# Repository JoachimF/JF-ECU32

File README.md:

# JF-ECU32
RC Jet Engine ECU

Details ici : https://www.usinages.com/threads/creation-dun-ecu-opensource-pour-micro-reacteur.160245/

## Environement
- VsCode
- IDF 5.0.8

## Démarrage du projet d'ECU opensource pour réacteurs

### Fonctionnalitées :

- Démarrage GAZ/KERO
- Fonctionnement du réacteur*
- Apprentissage du moteur*
- Surveillance des paramètres
- Redémarrage en vol*
- Log
- Interface WEB
- Ecran sans fil*
- Log sur MicroSd
- Baromètre

### Composants :
- Processeur ESP32
- Interface sonde K MAX31855
- INA218
- Max31855K
- BMP280
- MicroSD

### Entrées :
- Entrée 2S - 3S pour accus LIPO ou LIION
- Entrée PPM - Gaz ou SBUS
- Entrée PPM - AUX
- Entrée compte tours IR ou HALL
- Entrée sonde K (module MAX31865)
- INA219 courant de la bougie
- BMP280 pression / altitude

### Sorties :
- Sortie PWM/PPM 10A pour le moteur de démarrage
- Sortie PWM/PPM 10A pour la pompe ou ESC brushless
- Sortie PWM/PPM 10A pour ESC de pompe numéro 2 (fumigène ou redondance, comme sur les grandeurs)
- Sorties PWM pour 2 électrovannes (KERO/GAZ - KERO/KERO) 1A
- Sortie PWM pour une bougies Glow ou Kero 10A
- Sortie FPORT FRSky/Hott/Futaba (télémétrie)*

### Parties fonctionnelles :
 
 #### Entrées
 - Lecture des RPM
 - Lecture EGT
 - Lecture courant bougie
 - Lecture tension de batterie
 - Lecture Voie des gaz et voie aux
 
 #### Sortie   
 - Pilotage starter (PPM ou PWM)
 - Pilotage bougie
 - pilotage pompe1 (PPM ou PWM)
 - pilotage pompe2 (PPM ou PWM)
 - pilotage des vannes

#### Logiciel
 - Ecriture des logs (sur Spiffs pour le moment)
 - Calcul des deltas (EGT - RPM)
 - Calibration du démareur (Récupere les mini maxi en commande (%) et en RPM)
 - Préchauffage au gaz
 - Protection batterie trop faible ou trop haute en tension
 - Refroidissement de la turbine (action du démarreur)

### Parties à coder :
  - Lecture BMP280
  - Log sur MicroSD
  - fonction de démarrage du moteur
  - fonction de pilotage du moteur
  - fonction apprentissage du moteur
  - plein d'autres choses

*en cours de codage

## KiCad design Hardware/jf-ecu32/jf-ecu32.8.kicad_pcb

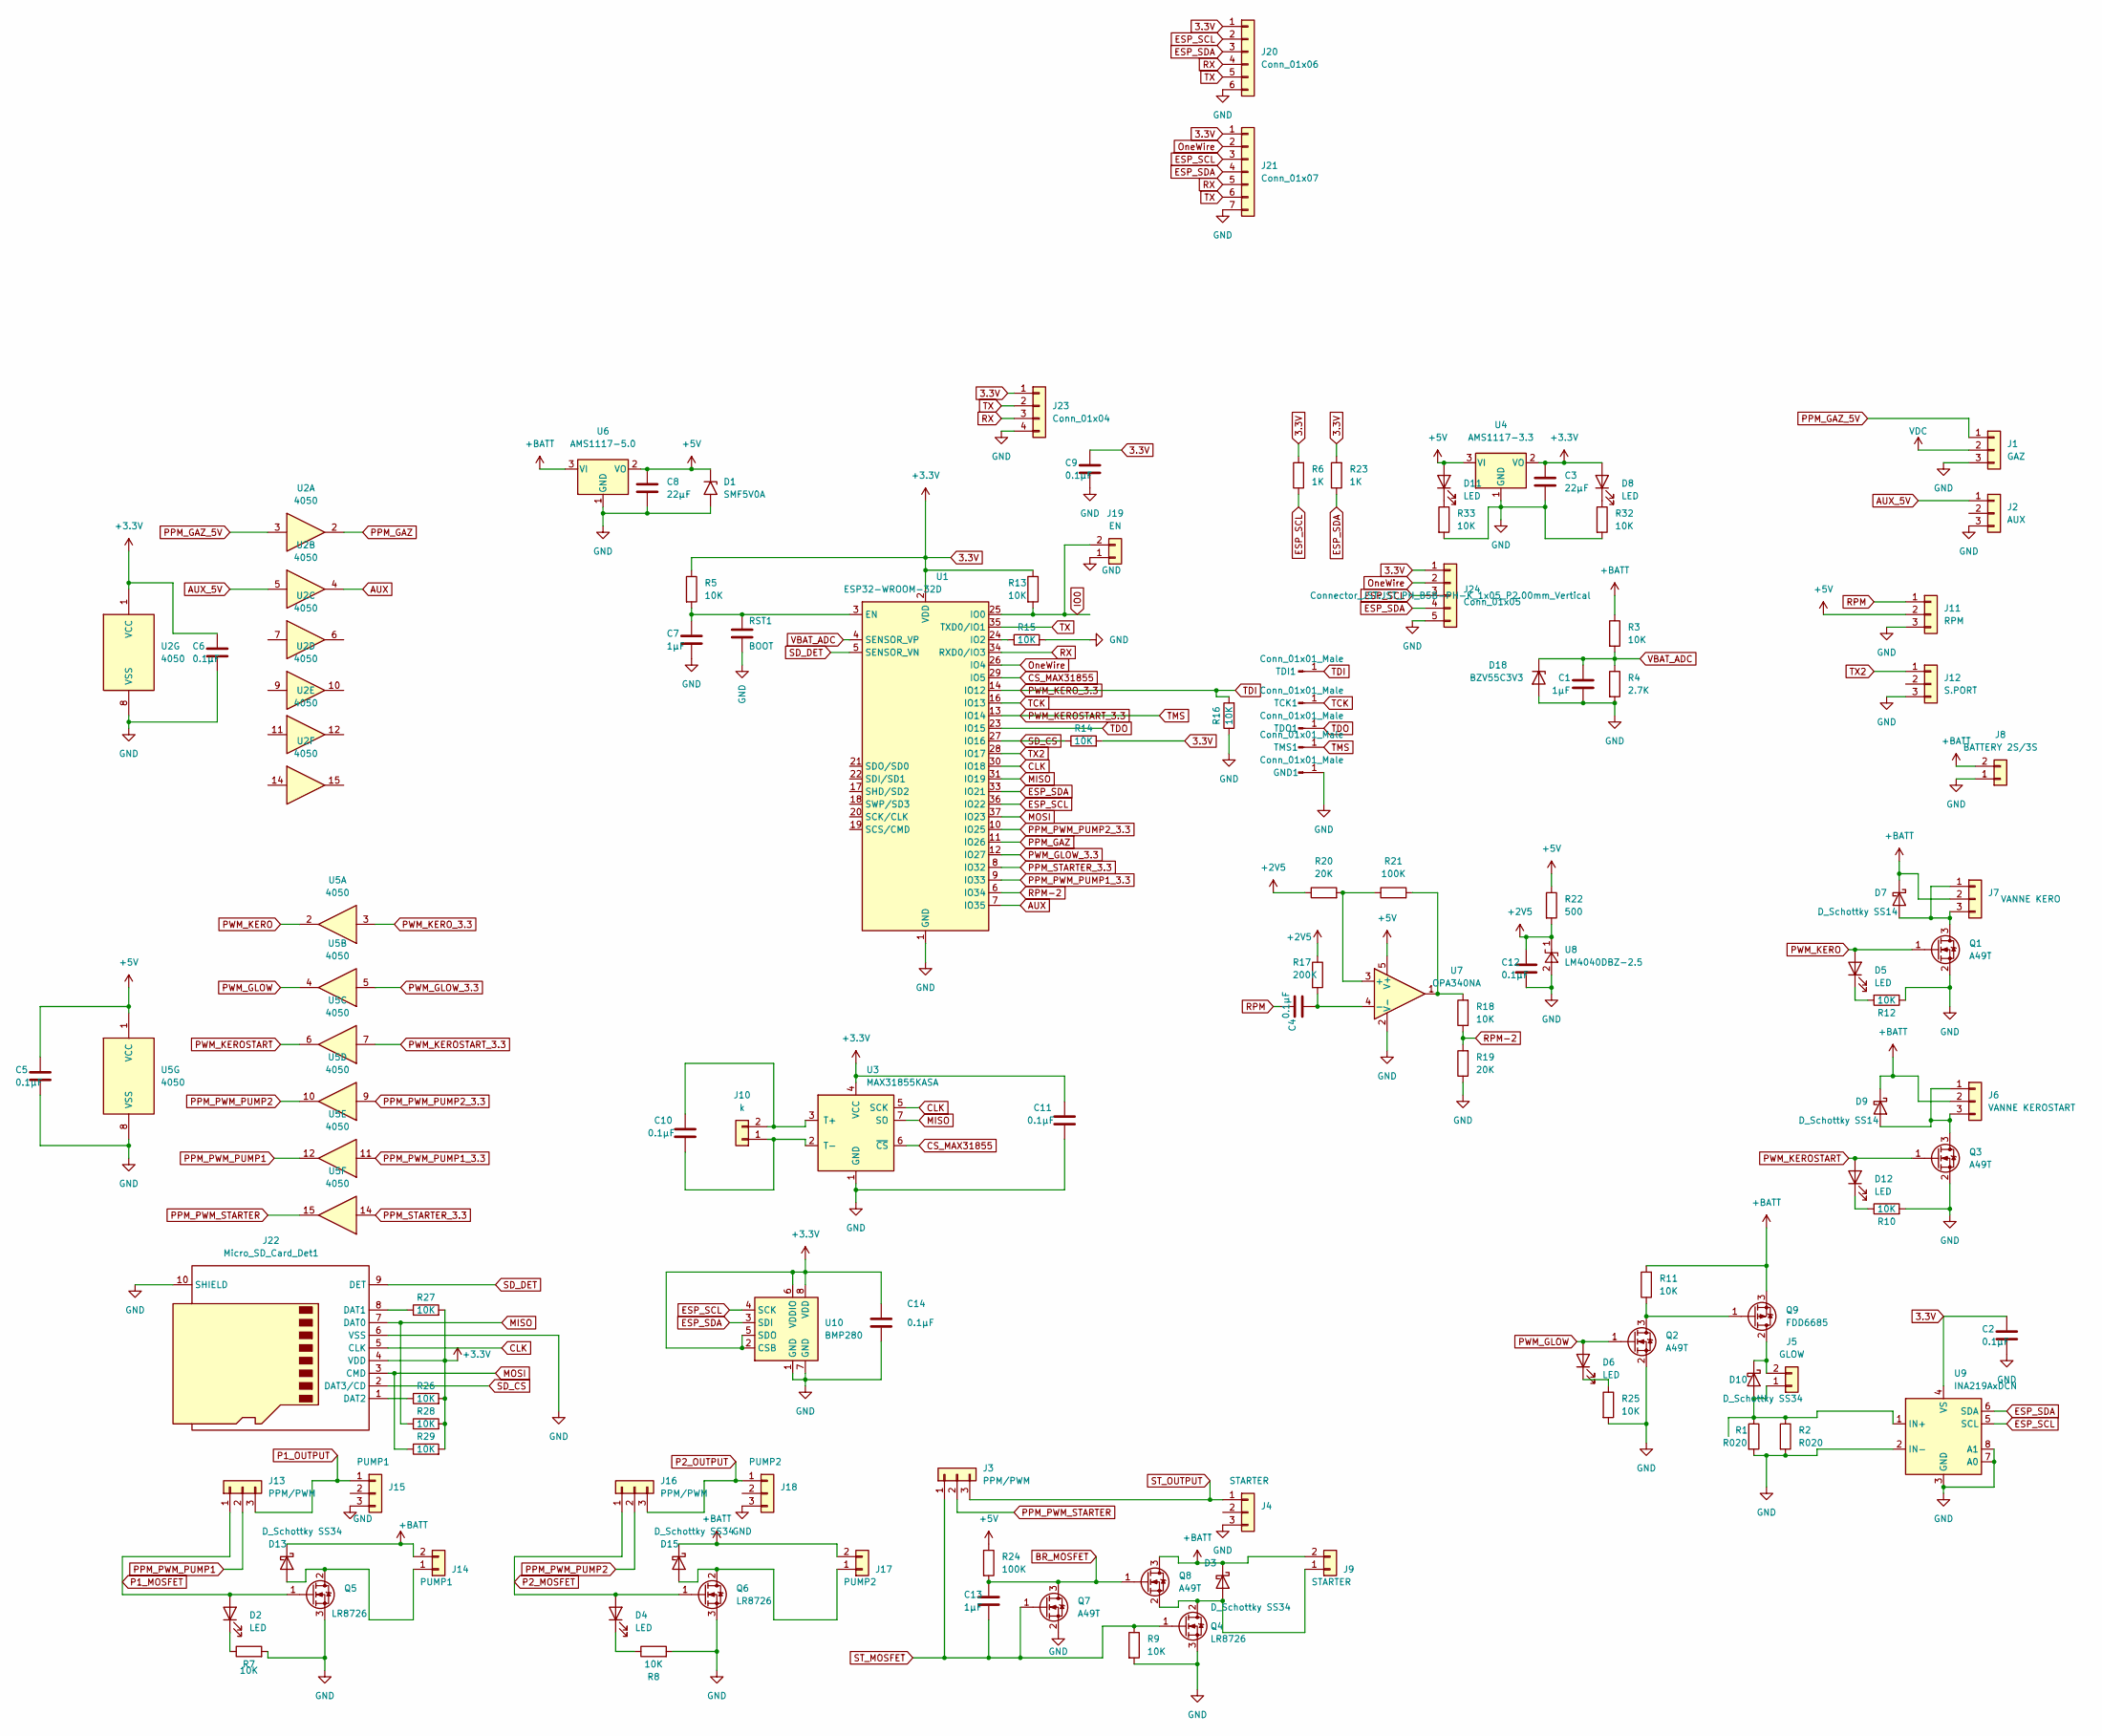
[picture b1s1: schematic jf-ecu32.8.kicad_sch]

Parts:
C1, C7, C13: 1µF; C_0603_1608Metric
C2, C4, C5, C6, C9, C10, C11, C12, C14: 0.1µF; C_0603_1608Metric
C3, C8: 22µF; CP_Elec_5x3
D1: SMF5V0A; D_SMF
D2, D4, D5, D6, D8, D11, D12: LED; LED_0603_1608Metric
D3, D10, D13, D15: D_Schottky SS34; D_SMA
D7, D9: D_Schottky SS14; D_SMA
D18: BZV55C3V3; D_MiniMELF
GND1: Conn_01x01_Male; PinHeader_1x01_P2.00mm_Vertical
J1: GAZ; PinHeader_1x03_P2.54mm_Vertical
J2: AUX; PinHeader_1x03_P2.54mm_Vertical
J3, J13, J16: PPM/PWM; PinHeader_1x03_P2.54mm_Vertical
J4: STARTER; PinHeader_1x03_P2.54mm_Vertical
J5: GLOW; AMASS_XT30U-F_1x02_P5.0mm_Vertical
J6: VANNE KEROSTART; PinHeader_1x03_P2.54mm_Vertical
J7: VANNE KERO; PinHeader_1x03_P2.54mm_Vertical
J8: BATTERY 2S/3S; AMASS_XT30U-M_1x02_P5.0mm_Vertical
J9: STARTER; AMASS_XT30U-F_1x02_P5.0mm_Vertical
J10: k; PinHeader_1x02_P2.54mm_Vertical
J11: RPM; PinHeader_1x03_P2.54mm_Vertical
J12: S.PORT; PinHeader_1x03_P2.54mm_Vertical
J14: PUMP1; AMASS_XT30U-F_1x02_P5.0mm_Vertical
J15: PUMP1; PinHeader_1x03_P2.54mm_Vertical
J17: PUMP2; AMASS_XT30U-F_1x02_P5.0mm_Vertical
J18: PUMP2; PinHeader_1x03_P2.54mm_Vertical
J19: EN; PinHeader_1x02_P2.54mm_Vertical
J20: Conn_01x06
J21: Conn_01x07
J22: Micro_SD_Card_Det1; J_SD_Card-micro_socket_A
J23: Conn_01x04; JST_PH_B4B-PH-K_1x04_P2.00mm_Vertical
J24: Conn_01x05; JST_PH_B5B-PH-K_1x05_P2.00mm_Vertical
Q1, Q2, Q3, Q7, Q8: A49T; SOT-23
Q4, Q5, Q6: LR8726; TO-252-2
Q9: FDD6685; TO-252-2
R1, R2: R020; R_2512_6332Metric
R3, R5, R7, R8, R9, R10, R11, R12, R13, R14, R15, R16, R18, R25, R26, R27, R28, R29, R32, R33: 10K; R_0603_1608Metric
R4: 2.7K; R_0603_1608Metric
R6, R23: 1K; R_0603_1608Metric
R17: 200K; R_0603_1608Metric
R19, R20: 20K; R_0603_1608Metric
R21, R24: 100K; R_0603_1608Metric
R22: 500; R_0603_1608Metric
RST1: BOOT; C_0603_1608Metric
TCK1: Conn_01x01_Male; PinHeader_1x01_P2.00mm_Vertical
TDI1: Conn_01x01_Male; PinHeader_1x01_P2.00mm_Vertical
TDO1: Conn_01x01_Male; PinHeader_1x01_P2.00mm_Vertical
TMS1: Conn_01x01_Male; PinHeader_1x01_P2.00mm_Vertical
U1: ESP32-WROOM-32D; ESP32-WROOM-32
U2, U5: 4050; SOP-16_4.4x10.4mm_P1.27mm
U3: MAX31855KASA; SOIC-8_3.9x4.9mm_P1.27mm
U4: AMS1117-3.3; SOT-223-3_TabPin2
U6: AMS1117-5.0; SOT-223-3_TabPin2
U7: OPA340NA; SOT-23-5
U8: LM4040DBZ-2.5; SOT-23
U9: INA219AxDCN; SOT-23-8
U10: BMP280; Bosch_LGA-8_2x2.5mm_P0.65mm_ClockwisePinNumbering

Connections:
3.3V: C2.1, C3.1, C6.1, C9.1, C11.1, C14.1, D8.2 (A), J20.1, J21.1, J22.4 (VDD), J23.1, J24.1, R5.1, R6.2, R13.1, R14.2, R23.2, R26.2, R27.2, R28.2, R29.2, U1.2 (VDD), U2.1 (VCC), U3.4 (VCC), U4.2 (VO), U9.4 (VS), U10.2 (CSB), U10.5 (SDO), U10.6 (VDDIO), U10.8 (VDD)
+2V5: C12.1, R17.1, R20.1, R22.2, U8.1 (K)
+5V: C5.1, C8.1, D1.1 (A1), D11.2 (A), J11.2, R22.1, R24.1, U4.3 (VI), U5.1 (VCC), U6.2 (VO), U7.5 (V+)
+BATT: D3.1 (K), D7.1 (K), D9.1 (K), D13.1 (K), D15.1 (K), J6.2, J7.2, J8.2, J9.2, J14.2, J17.2, Q8.3 (D), Q9.3 (S), R3.1, R11.2, U6.3 (VI)
AUX: U1.7 (IO35), U2.4
AUX_5V: J2.1, U2.5
BR_MOSFET: C13.1, Q7.3 (D), Q8.1 (G), R24.2
CLK: J22.5 (CLK), U1.30 (IO18), U3.5 (SCK)
CS_MAX31855: U1.29 (IO5), U3.6 (~CS)
ESP_SCL: J20.2, J21.3, J24.3, R6.1, U1.36 (IO22), U9.5 (SCL), U10.4 (SCK)
ESP_SDA: J20.3, J21.4, J24.4, R23.1, U1.33 (IO21), U9.6 (SDA), U10.3 (SDI)
GND: C1.2, C2.2, C3.2, C5.2, C6.2, C7.2, C8.2, C9.2, C11.2, C12.2, C14.2, D1.2 (A2), D18.2 (A), GND1.1, J1.3, J2.3, J4.3, J8.1, J11.3, J12.3, J15.3, J18.3, J19.1, J20.6, J21.7, J22.6 (VSS), J22.10 (SHIELD), J23.4, J24.5, Q1.2 (S), Q2.2 (S), Q3.2 (S), Q4.3 (S), Q5.3 (S), Q6.3 (S), Q7.2 (S), R1.2, R2.2, R4.2, R7.2, R8.2, R9.2, R10.2, R12.1, R15.2, R16.1, R19.1, R25.2, R32.2, R33.2, RST1.2, U1.1 (GND), U1.15 (GND), U1.38 (GND), U1.39 (GND), U2.8 (VSS), U3.1 (GND), U4.1 (GND), U5.8 (VSS), U6.1 (GND), U7.2 (V-), U8.2 (A), U9.2 (IN-), U9.3 (GND), U9.7 (A0), U9.8 (A1), U10.1 (GND), U10.7 (GND)
IO0: J19.2, R13.2, U1.25 (IO0)
MISO: J22.7 (DAT0), R28.1, U1.31 (IO19), U3.7 (SO)
MOSI: J22.3 (CMD), R29.1, U1.37 (IO23)
unnamed: D2.1 (K), R7.1
unnamed: D3.2 (A), J9.1, Q4.2 (D), Q8.2 (S)
unnamed: D4.1 (K), R8.1
unnamed: D5.1 (K), R12.2
unnamed: D6.1 (K), R25.1
unnamed: D7.2 (A), J7.1, J7.3, Q1.3 (D)
unnamed: D8.1 (K), R32.1
unnamed: D9.2 (A), J6.1, J6.3, Q3.3 (D)
unnamed: D10.2 (A), J5.1, R1.1, R2.1, U9.1 (IN+)
unnamed: D10.1 (K), J5.2, Q9.2 (D)
unnamed: D11.1 (K), R33.1
unnamed: D12.1 (K), R10.1
unnamed: D13.2 (A), J14.1, Q5.2 (D)
unnamed: D15.2 (A), J17.1, Q6.2 (D)
unnamed: C10.2, J10.1, U3.2 (T-)
unnamed: C10.1, J10.2, U3.3 (T+)
unnamed: J22.8 (DAT1), R27.1
unnamed: J22.1 (DAT2), R26.1
unnamed: Q2.3 (D), Q9.1 (G), R11.1
unnamed: R18.2, R21.2, U7.1
unnamed: C7.1, R5.2, RST1.1, U1.3 (EN)
unnamed: R15.1, U1.24 (IO2)
unnamed: R20.2, R21.1, U7.3 (+)
unnamed: C4.2, R17.2, U7.4 (-)
OneWire: J21.2, J24.2, U1.26 (IO4)
P1_MOSFET: D2.2 (A), J13.1, Q5.1 (G)
P1_OUTPUT: J13.3, J15.1
P2_MOSFET: D4.2 (A), J16.1, Q6.1 (G)
P2_OUTPUT: J16.3, J18.1
PPM_GAZ: U1.11 (IO26), U2.2
PPM_GAZ_5V: J1.1, U2.3
PPM_PWM_PUMP1: J13.2, U5.12
PPM_PWM_PUMP1_3.3: U1.9 (IO33), U5.11
PPM_PWM_PUMP2: J16.2, U5.10
PPM_PWM_PUMP2_3.3: U1.10 (IO25), U5.9
PPM_PWM_STARTER: J3.2, U5.15
PPM_STARTER_3.3: U1.8 (IO32), U5.14
PWM_GLOW: D6.2 (A), Q2.1 (G), U5.4
PWM_GLOW_3.3: U1.12 (IO27), U5.5
PWM_KERO: D5.2 (A), Q1.1 (G), U5.2
PWM_KEROSTART: D12.2 (A), Q3.1 (G), U5.6
PWM_KEROSTART_3.3: TMS1.1, U1.13 (IO14), U5.7
PWM_KERO_3.3: R16.2, TDI1.1, U1.14 (IO12), U5.3
RPM: C4.1, J11.1
RPM-2: R18.1, R19.2, U1.6 (IO34)
RX: J20.4, J21.5, J23.3, U1.34 (RXD0/IO3)
SD_CS: J22.2 (DAT3/CD), R14.1, U1.27 (IO16)
SD_DET: J22.9 (DET), U1.5 (SENSOR_VN)
ST_MOSFET: C13.2, J3.1, Q4.1 (G), Q7.1 (G), R9.1
ST_OUTPUT: J3.3, J4.1
TCK: TCK1.1, U1.16 (IO13)
TDO: TDO1.1, U1.23 (IO15)
TX: J20.5, J21.6, J23.2, U1.35 (TXD0/IO1)
TX2: J12.1, U1.28 (IO17)
VBAT_ADC: C1.1, D18.1 (K), R3.2, R4.1, U1.4 (SENSOR_VP)
VDC: J1.2

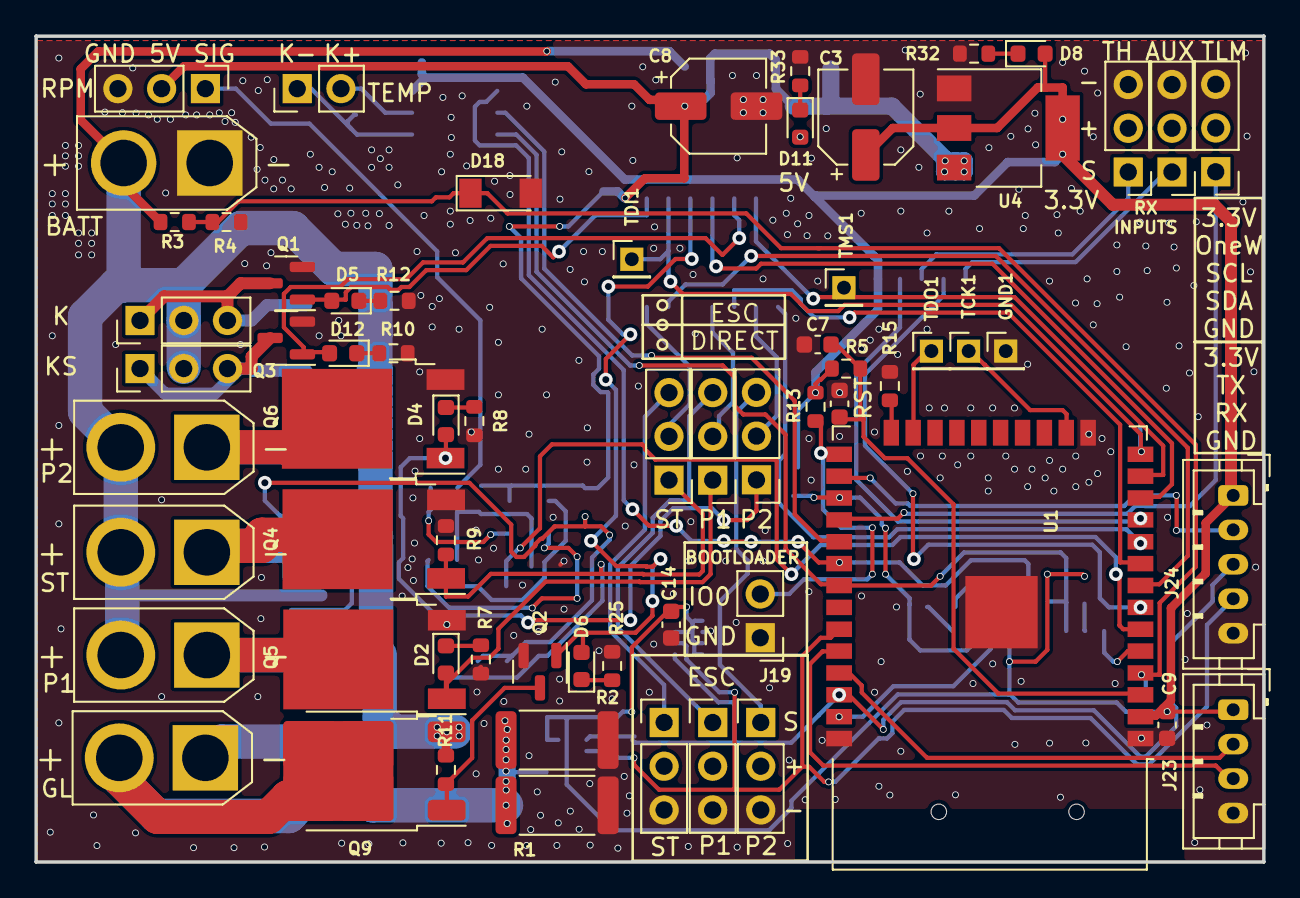
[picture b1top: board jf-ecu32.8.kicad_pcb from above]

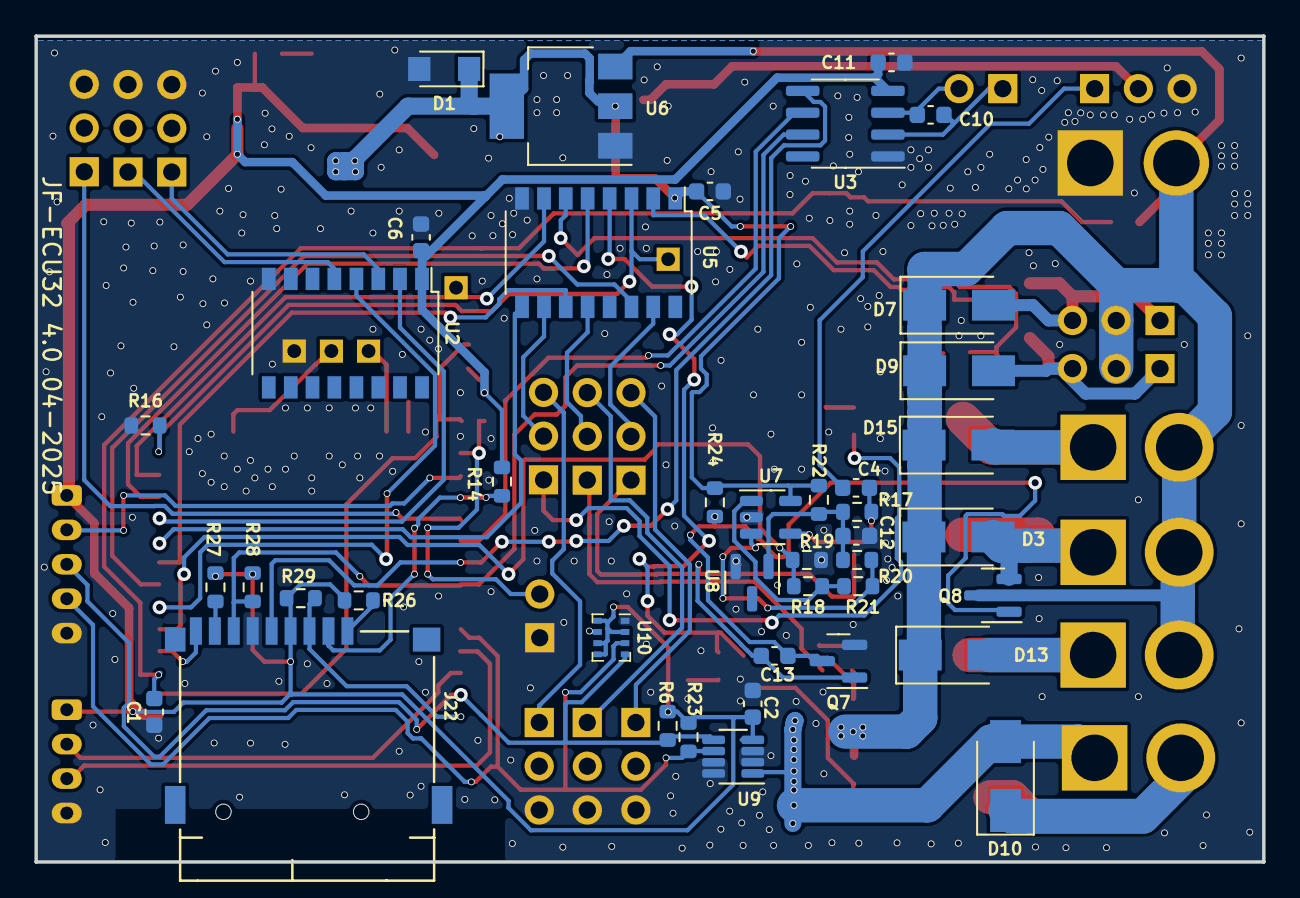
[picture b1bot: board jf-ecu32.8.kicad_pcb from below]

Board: 2 copper layers, 71.3 x 48.0 mm, 107 parts (42 on the bottom side), 70 nets.

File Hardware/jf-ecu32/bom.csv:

"Reference","Value","Do Not Place","Exclude from BOM","Exclude from Board","Exclude from Simulation"
"C1","1µF","","","",""
"C2","0.1µF","","","",""
"C3","22µF","","","",""
"C4","0.1µF","","","",""
"C5","0.1µF","","","",""
"C6","0.1µF","","","",""
"C7","1µF","","","",""
"C8","22µF","","","",""
"C9","0.1µF","","","",""
"C10","0.1µF","","","",""
"C11","0.1µF","","","",""
"C12","0.1µF","","","",""
"C13","1µF","","","",""
"C14","0.1µF","","","",""
"D1","SMF5V0A","","","",""
"D2","LED","","","",""
"D3","D_Schottky SS34","","","",""
"D4","LED","","","",""
"D5","LED","","","",""
"D6","LED","","","",""
"D7","D_Schottky SS14","","","",""
"D8","LED","","","",""
"D9","D_Schottky SS14","","","",""
"D10","D_Schottky SS34","","","",""
"D11","LED","","","",""
"D12","LED","","","",""
"D13","D_Schottky SS34","","","",""
"D15","D_Schottky SS34","","","",""
"D18","BZV55C3V3","","","",""
"GND1","Conn_01x01_Male","","","",""
"J1","GAZ","","","",""
"J2","AUX","","","",""
"J3","PPM/PWM","","","",""
"J4","STARTER","","","",""
"J5","GLOW","","","",""
"J6","VANNE KEROSTART","","","",""
"J7","VANNE KERO","","","",""
"J8","BATTERY 2S/3S","","","",""
"J9","STARTER","","","",""
"J10","k","","","",""
"J11","RPM","","","",""
"J12","S.PORT","","","",""
"J13","PPM/PWM","","","",""
"J14","PUMP1","","","",""
"J15","PUMP1","","","",""
"J16","PPM/PWM","","","",""
"J17","PUMP2","","","",""
"J18","PUMP2","","","",""
"J19","EN","","","",""
"J20","Conn_01x06","","","",""
"J21","Conn_01x07","","","",""
"J22","Micro_SD_Card_Det1","","","",""
"J23","Conn_01x04","","","",""
"J24","Conn_01x05","","","",""
"Q1","A49T","","","",""
"Q2","A49T","","","",""
"Q3","A49T","","","",""
"Q4","LR8726","","","",""
"Q5","LR8726","","","",""
"Q6","LR8726","","","",""
"Q7","A49T","","","",""
"Q8","A49T","","","",""
"Q9","FDD6685","","","",""
"R1","R020","","","",""
"R2","R020","","","",""
"R3","10K","","","",""
"R4","2.7K","","","",""
"R5","10K","","","",""
"R6","1K","","","",""
"R7","10K","","","",""
"R8","10K","","","",""
"R9","10K","","","",""
"R10","10K","","","",""
"R11","10K","","","",""
"R12","10K","","","",""
"R13","10K","","","",""
"R14","10K","","","",""
"R15","10K","","","",""
"R16","10K","","","",""
"R17","200K","","","",""
"R18","10K","","","",""
"R19","20K","","","",""
"R20","20K","","","",""
"R21","100K","","","",""
"R22","500","","","",""
"R23","1K","","","",""
"R24","100K","","","",""
"R25","10K","","","",""
"R26","10K","","","",""
"R27","10K","","","",""
"R28","10K","","","",""
"R29","10K","","","",""
"R32","10K","","","",""
"R33","10K","","","",""
"RST1","BOOT","","","",""
"TCK1","Conn_01x01_Male","","","",""
"TDI1","Conn_01x01_Male","","","",""
"TDO1","Conn_01x01_Male","","","",""
"TMS1","Conn_01x01_Male","","","",""
"U1","ESP32-WROOM-32D","","","",""
"U2","4050","","","",""
"U3","MAX31855KASA","","","",""
"U4","AMS1117-3.3","","","",""
"U5","4050","","","",""
"U6","AMS1117-5.0","","","",""
"U7","OPA340NA","","","",""
"U8","LM4040DBZ-2.5","","","",""
"U9","INA219AxDCN","","","",""
"U10","BMP280","","","",""

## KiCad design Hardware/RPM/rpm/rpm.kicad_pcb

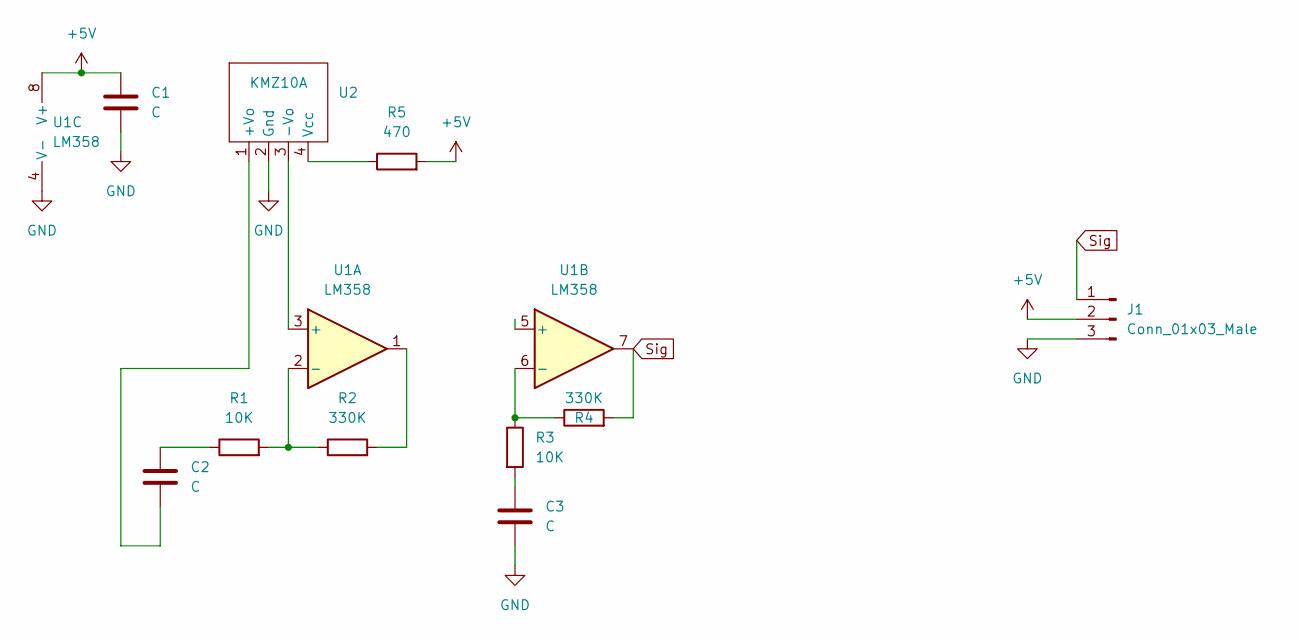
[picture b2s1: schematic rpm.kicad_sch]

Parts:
C1, C2, C3: C; C_0805_2012Metric
J1: Conn_01x03_Male; PinHeader_1x03_P2.54mm_Vertical
R1, R3: 10K; R_0805_2012Metric
R2, R4: 330K; R_0805_2012Metric
R5: 470; R_0805_2012Metric
U1: LM358; SSOP-8_3.9x5.05mm_P1.27mm
U2: KMZ10A; PinHeader_1x04_P1.27mm_Vertical

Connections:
+5V: C1.1, J1.2, R5.2, U1.8 (V+)
GND: C1.2, C3.2, J1.3, U1.4 (V-), U2.2 (Gnd)
unnamed: C2.1, R1.1
unnamed: C3.1, R3.2
unnamed: R1.2, R2.1, U1.2 (-)
unnamed: R2.2, U1.1
unnamed: R3.1, R4.1, U1.6 (-)
unnamed: R5.1, U2.4 (Vcc)
unnamed: U1.3 (+), U2.3 (-Vo)
unnamed: C2.2, U2.1 (+Vo)
Sig: J1.1, R4.2, U1.7

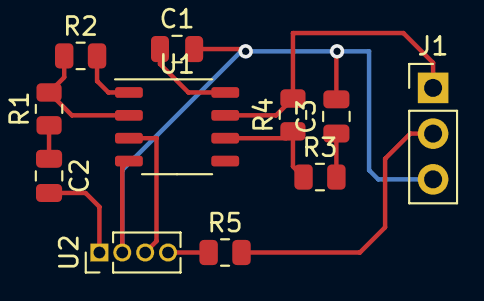
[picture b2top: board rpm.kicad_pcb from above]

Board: 2 copper layers, 11 parts (0 on the bottom side), 11 nets.

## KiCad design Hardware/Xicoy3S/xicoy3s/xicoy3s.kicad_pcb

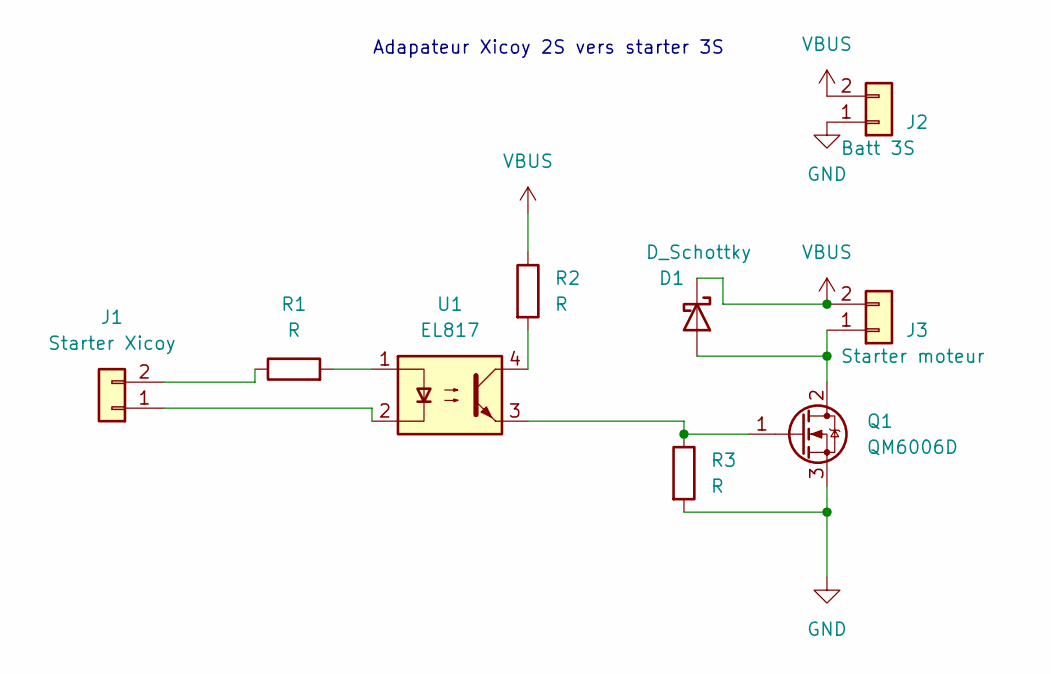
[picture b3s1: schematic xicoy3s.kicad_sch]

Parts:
D1: D_Schottky; D_SMA
J1: Starter Xicoy; PinHeader_1x02_P2.54mm_Vertical
J2: Batt 3S; AMASS_XT30U-F_1x02_P5.0mm_Vertical
J3: Starter moteur; AMASS_XT30U-F_1x02_P5.0mm_Vertical
Q1: QM6006D; TO-252-2
R1, R2, R3: R; R_0603_1608Metric
U1: EL817; SOP-4_3.8x4.1mm_P2.54mm

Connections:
GND: J2.1, Q1.3 (S), R3.2
unnamed: D1.2 (A), J3.1, Q1.2 (D)
unnamed: J1.1, U1.2
unnamed: J1.2, R1.1
unnamed: Q1.1 (G), R3.1, U1.3
unnamed: R1.2, U1.1
unnamed: R2.2, U1.4
VBUS: D1.1 (K), J2.2, J3.2, R2.1

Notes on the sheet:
Adapateur Xicoy 2S vers starter 3S

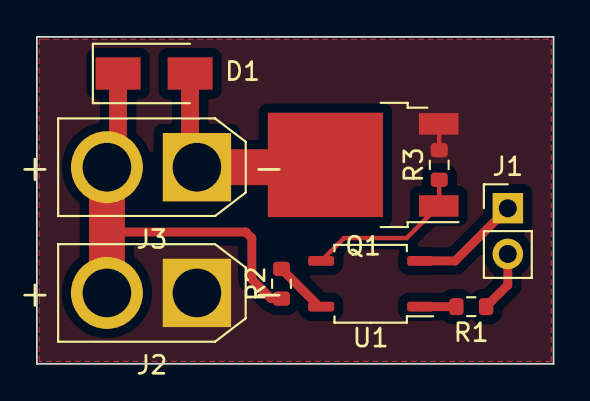
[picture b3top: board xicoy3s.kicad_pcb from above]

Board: 2 copper layers, 28.7 x 18.2 mm, 9 parts (0 on the bottom side), 8 nets.

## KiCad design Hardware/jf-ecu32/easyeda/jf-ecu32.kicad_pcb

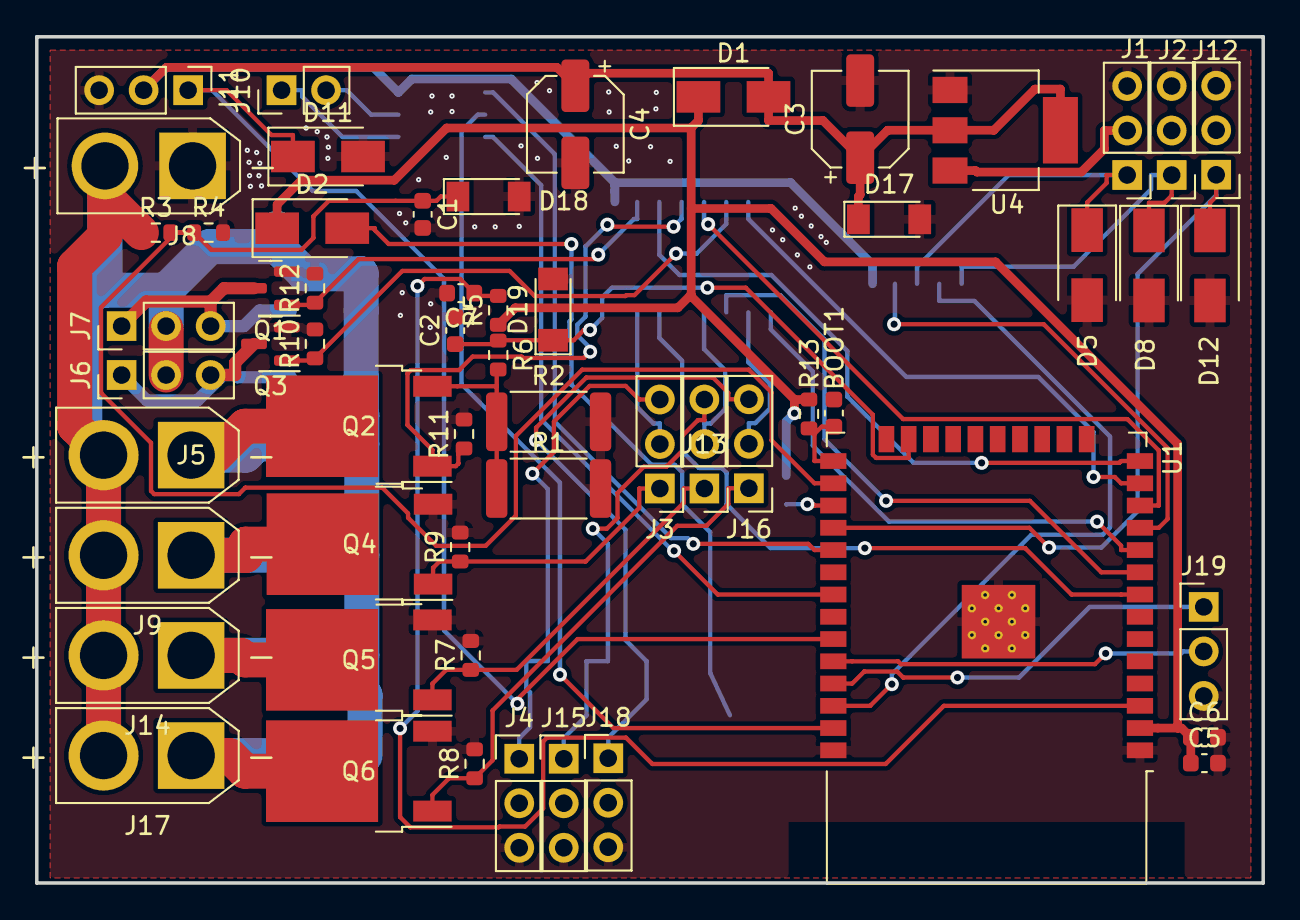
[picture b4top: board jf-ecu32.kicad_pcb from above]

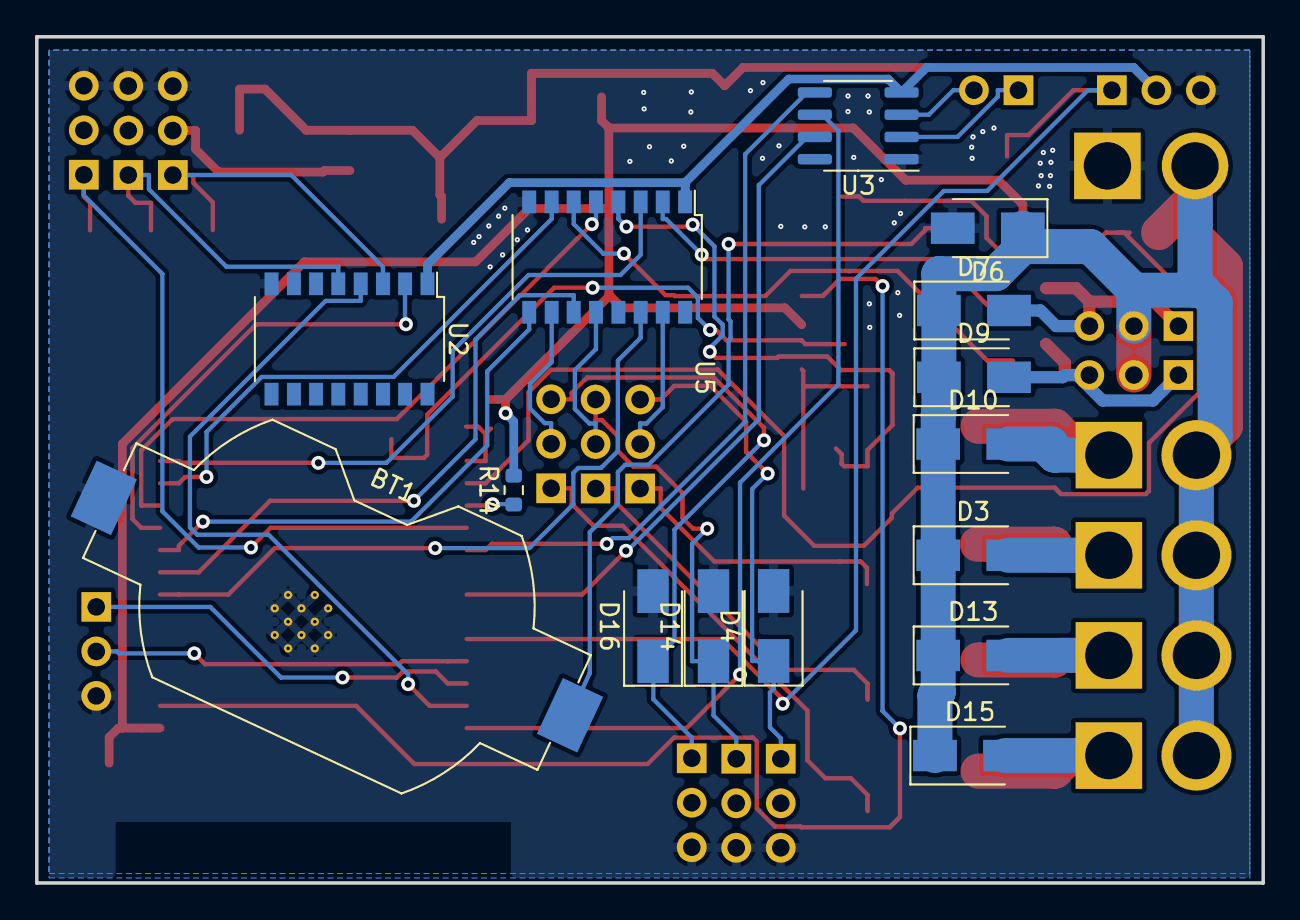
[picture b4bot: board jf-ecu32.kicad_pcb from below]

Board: 2 copper layers, 70.0 x 48.3 mm, 72 parts (15 on the bottom side), 49 nets.

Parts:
BOOT1: BOOT; C_0603_1608Metric
BT1: Battery_Cell; BatteryHolder_Keystone_1058_1x2032
C1, C7: 1µF; C_0603_1608Metric
C2: 10nF; C_0603_1608Metric
C3: 0.1µF; CP_Elec_5x3
C4: 22µF; CP_Elec_5x3
C5, C6: C; C_0603_1608Metric
D1, D2, D3, D4, D5, D6, D7, D8, D9, D10, D11, D12, D13, D14, D15, D16: D_Schottky; D_SMA
D17, D18, D19: BZV55C3V3; D_MiniMELF
J1: GAZ; PinHeader_1x03_P2.54mm_Vertical
J2: AUX; PinHeader_1x03_P2.54mm_Vertical
J3, J13, J16: PPM/PWM; PinHeader_1x03_P2.54mm_Vertical
J4: STARTER; PinHeader_1x03_P2.54mm_Vertical
J5: GLOW; AMASS_XT30U-F_1x02_P5.0mm_Vertical
J6: VANNE KEROSTART; PinHeader_1x03_P2.54mm_Vertical
J7: VANNE KERO; PinHeader_1x03_P2.54mm_Vertical
J8: BATTERY 2S/3S; AMASS_XT30U-M_1x02_P5.0mm_Vertical
J9: STARTER; AMASS_XT30U-F_1x02_P5.0mm_Vertical
J10: k; PinHeader_1x02_P2.54mm_Vertical
J11: RPM; PinHeader_1x03_P2.54mm_Vertical
J12: S.PORT; PinHeader_1x03_P2.54mm_Vertical
J14: PUMP1; AMASS_XT30U-F_1x02_P5.0mm_Vertical
J15: PUMP1; PinHeader_1x03_P2.54mm_Vertical
J17: PUMP2; AMASS_XT30U-F_1x02_P5.0mm_Vertical
J18: PUMP2; PinHeader_1x03_P2.54mm_Vertical
J19: UART0; PinHeader_1x03_P2.54mm_Vertical
Q1, Q3: AO3400A; SOT-23
Q2, Q4, Q5, Q6: QM6006D; TO-252-2
R1, R2: R020; R_2512_6332Metric
R3, R5, R6, R13, R14: 10K; R_0603_1608Metric
R4: 2.7K; R_0603_1608Metric
R7, R8, R9, R10, R11, R12: R; R_0603_1608Metric
U1: ESP32-WROOM-32D; ESP32-WROOM-32
U2, U5: 4050; SOP-16_4.4x10.4mm_P1.27mm
U3: MAX31855KASA; SOIC-8_3.9x4.9mm_P1.27mm
U4: AMS1117-3.3; SOT-223-3_TabPin2

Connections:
+3.3V: C3.1, C4.1, D1.2 (A), D17.1 (K), J11.2, U2.1 (VCC), U3.4 (VCC), U4.2 (VO), U5.1 (VCC)
+BATT: D3.1 (K), D6.1 (K), D7.1 (K), D9.1 (K), D10.1 (K), D13.1 (K), D15.1 (K), J5.2, J6.2, J7.2, J8.2, J9.2, J14.2, J17.2, R3.1
AUX: U1.36 (IO22), U2.4
AUX_5V: D8.1 (K), J2.1, U2.5
CLK: U1.29 (IO5), U3.5 (SCK)
CS: U1.37 (IO23), U3.6 (~CS)
GLOW_CURRENT: C2.1, D19.1 (K), R6.1, U1.23 (IO15)
GND: BOOT1.2, BT1.2 (-), C1.2, C2.2, C3.2, C4.2, C5.2, C6.2, C7.2, D4.2 (A), D5.2 (A), D6.2 (A), D8.2 (A), D11.2 (A), D12.2 (A), D14.2 (A), D16.2 (A), D17.2 (A), D18.2 (A), D19.2 (A), J1.3, J2.3, J4.3, J8.1, J11.3, J12.3, J15.3, J18.3, J19.3, Q1.2 (S), Q3.2 (S), Q4.3 (S), Q5.3 (S), Q6.3 (S), R1.2, R2.2, R4.2, R7.2, R8.2, R9.2, R10.2, R11.2, R12.2, U1.1 (GND), U1.15 (GND), U1.38 (GND), U1.39 (GND), U2.8 (VSS), U3.1 (GND), U4.1 (GND), U5.8 (VSS)
MISO: U1.31 (IO19), U3.7 (SO)
unnamed: BT1.1 (+), D2.2 (A)
unnamed: D3.2 (A), J9.1, Q4.2 (D)
unnamed: D4.1 (K), J3.3, J4.1
unnamed: D7.2 (A), J7.1, J7.3, Q1.3 (D)
unnamed: D9.2 (A), J6.1, J6.3, Q3.3 (D)
unnamed: D10.2 (A), J5.1, Q2.2 (D)
unnamed: D13.2 (A), J14.1, Q5.2 (D)
unnamed: D14.1 (K), J13.3, J15.1
unnamed: D15.2 (A), J17.1, Q6.2 (D)
unnamed: D16.1 (K), J16.3, J18.1
unnamed: J3.1, Q4.1 (G), R9.1
unnamed: J10.1, U3.2 (T-)
unnamed: J10.2, U3.3 (T+)
unnamed: J13.1, Q5.1 (G), R7.1
unnamed: J16.1, Q6.1 (G), R8.1
unnamed: Q2.3 (S), R1.1, R2.1, R6.2
unnamed: C7.1, R5.2, U1.3 (EN)
unnamed: BOOT1.1, R13.2, U1.25 (IO0)
unnamed: R14.1, U1.27 (IO16)
unnamed: J19.2, U1.34 (RXD0/IO3)
unnamed: J19.1, U1.35 (TXD0/IO1)
PPM_GAZ: U1.11 (IO26), U2.2
PPM_GAZ_5V: D5.1 (K), J1.1, U2.3
PPM_PWM_PUMP1: J13.2, U5.12
PPM_PWM_PUMP1_3.3: U1.9 (IO33), U5.11
PPM_PWM_PUMP2: J16.2, U5.10
PPM_PWM_PUMP2_3.3: U1.10 (IO25), U5.9
PPM_PWM_STARTER: J3.2, U5.15
PPM_STARTER_3.3: U1.8 (IO32), U5.14
PWM_GLOW: Q2.1 (G), R11.1, U5.4
PWM_GLOW_3.3: U1.12 (IO27), U5.5
PWM_KERO: Q1.1 (G), R12.1, U5.2
PWM_KEROSTART: Q3.1 (G), R10.1, U5.6
PWM_KEROSTART_3.3: U1.13 (IO14), U5.7
PWM_KERO_3.3: U1.14 (IO12), U5.3
RPM: D11.1 (K), J11.1, U1.33 (IO21)
TX2: D12.1 (K), J12.1, U1.28 (IO17)
VBAT_ADC: C1.1, D18.1 (K), R3.2, R4.1, U1.26 (IO4)
VDC: J1.2, U4.3 (VI)
V_CPU: C5.1, C6.1, D1.1 (K), D2.1 (K), R5.1, R13.1, R14.2, U1.2 (VDD)

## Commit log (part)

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2022-12-04 Update hardware
2022-12-27 Ajout des nouveautés
2022-12-30 Derniere Maj
2023-01-03 New functions
2023-01-06 ignore
2023-01-06 build
2023-01-07 Updates PPM & PWM OK
2023-01-09 PCB update
2023-03-13 SCH + PCB
2023-03-13 Peripherals
2023-04-01 Inputs
2023-04-02 Inputs
    RC input and RPM OK
2023-04-02 All inputs and outputs OK
2023-04-04 Errors catch module
2023-04-14 Dynamic gauges RPM & EGT
2023-04-14 Error reports update
2023-04-19 PCB V2
2023-04-19 PCB V2 Final
2023-09-07 Test V2 board ALL ok except RPM
2023-09-08 PCB V3
2023-09-19 RPM problem
2024-08-05 Préparation de la V3
    Ajout d'un ampli op pour la lecture des RPM et d'un capteur de courant pour la bougie.
    Correction de l'alimentation de la bougie.
2024-08-05 Début de modification de code pour le PCB V3
2024-08-05 Correction des erreur de PCB
2024-09-20 PCB Kicad 7
2024-09-24 V3
    DS18B20
2024-10-08 Multilangue
2024-10-13 Dev chart
2024-10-14 Dev web
2024-10-21 PCB + SRC
2024-11-24 Test imu
2025-04-02 Test Carte V3 - Maj vers V4
2025-04-03 PCB V4 updated
    PCB V4
    File server
    Glow current read
    Voltage Read
    Starter calibration working
    Many links corrected
2025-04-03 Minor bugs
2025-04-06 Log system improvements
    Multiple files, on second spiffs partifion
2025-04-12 Logs and deltas
2025-04-13 Added MicroSD and BMP280
2025-04-13 SDCARD
2025-04-14 Logs moved to SDCard
2025-04-15 PCB RPM Filter adjusted
2025-04-19 Log on SD or SPIFFS
2026-04-29 Kicad 8 & IDF 5.2.6
